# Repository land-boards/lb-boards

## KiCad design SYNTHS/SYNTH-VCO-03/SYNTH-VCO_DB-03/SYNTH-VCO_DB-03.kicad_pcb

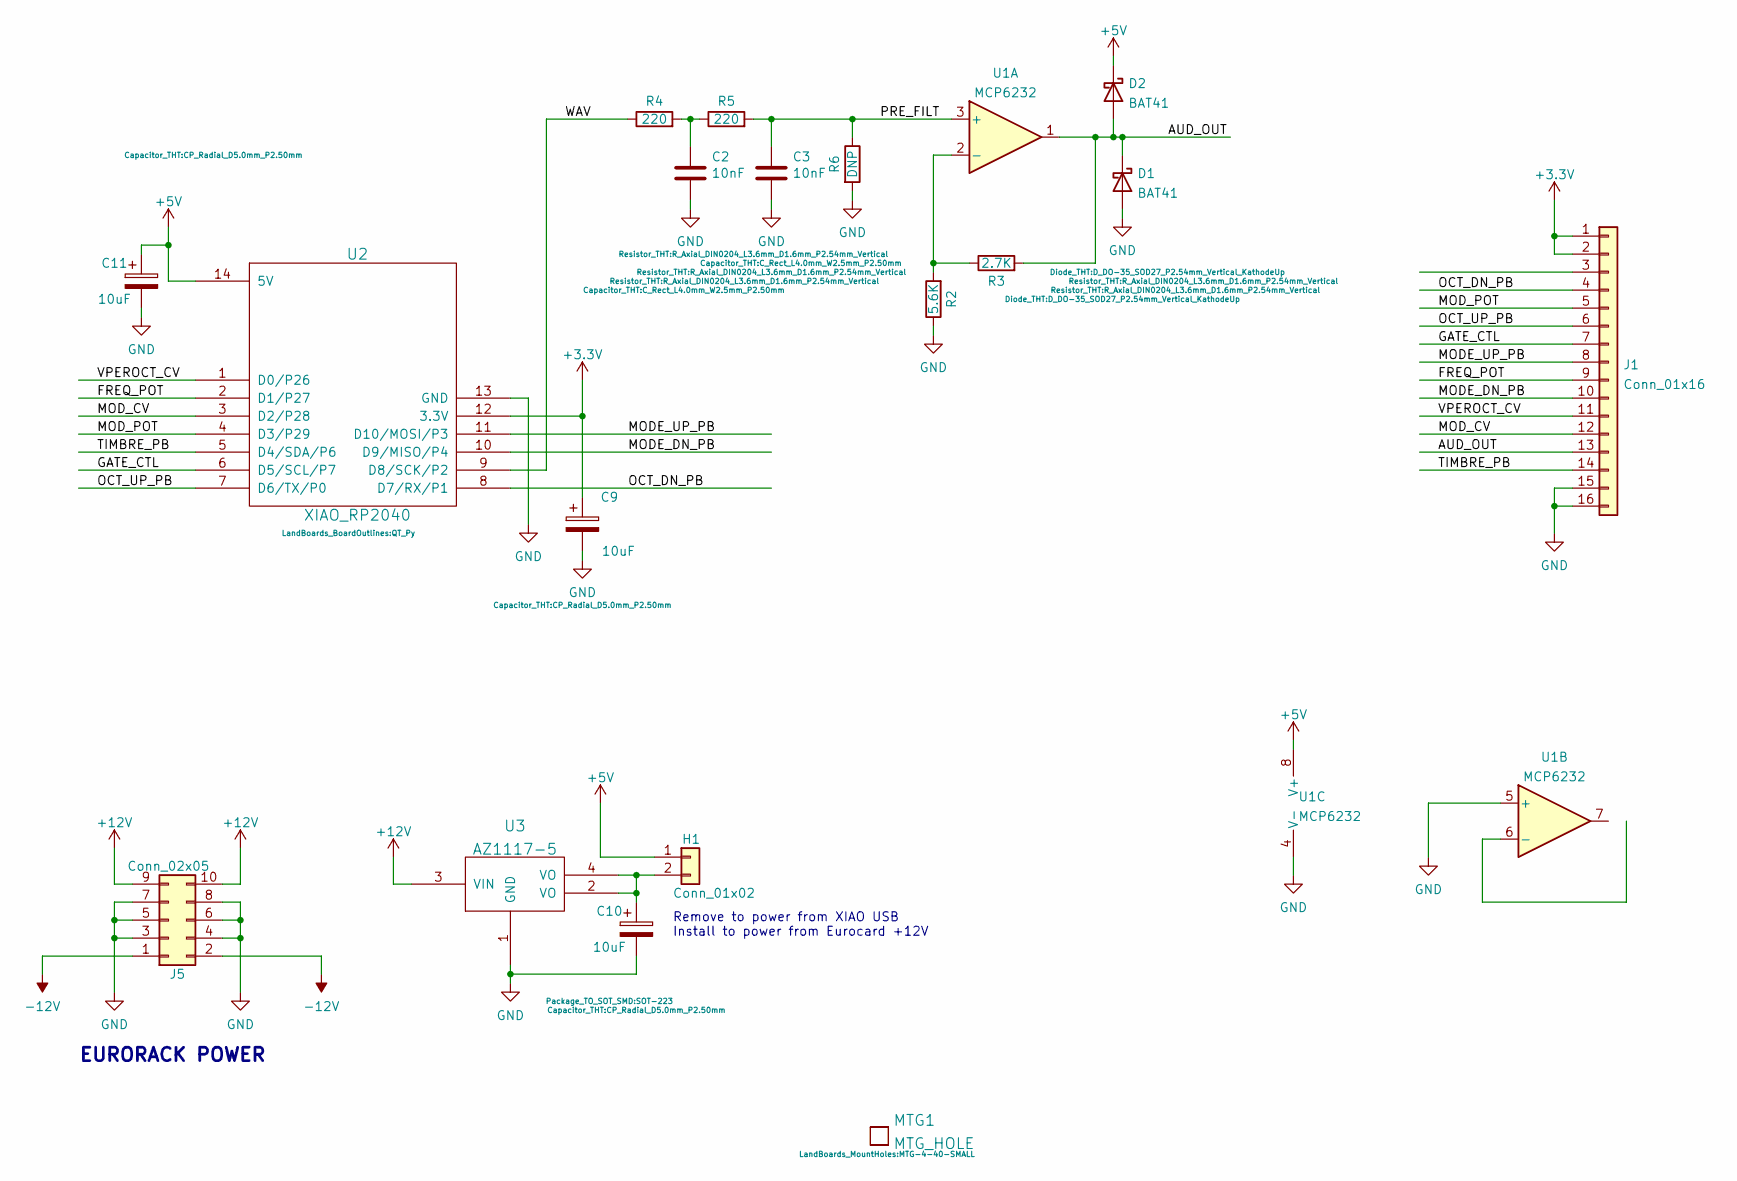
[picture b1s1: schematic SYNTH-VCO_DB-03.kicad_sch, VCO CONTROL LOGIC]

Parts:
C2, C3: 10nF; C_Rect_L4.0mm_W2.5mm_P2.50mm
C9, C10, C11: 10uF; CP_Radial_D5.0mm_P2.50mm
D1, D2: BAT41; D_DO-35_SOD27_P2.54mm_Vertical_KathodeUp
H1: Conn_01x02; PinHeader_1x02_P2.54mm_Vertical
J1: Conn_01x16; PinHeader_2x08_P2.54mm_Vertical
J5: Conn_02x05; IDC-Header_2x05_P2.54mm_Vertical
MTG1: MTG_HOLE; MTG-4-40-SMALL
R2: 5.6K; R_Axial_DIN0204_L3.6mm_D1.6mm_P2.54mm_Vertical
R3: 2.7K; R_Axial_DIN0204_L3.6mm_D1.6mm_P2.54mm_Vertical
R4, R5: 220; R_Axial_DIN0204_L3.6mm_D1.6mm_P2.54mm_Vertical
R6: DNP; R_Axial_DIN0204_L3.6mm_D1.6mm_P2.54mm_Vertical
U1: MCP6232; DIP-8_W7.62mm
U2: XIAO_RP2040; QT_Py
U3: AZ1117-5; SOT-223

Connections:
+3V3: C9.1, J1.1, J1.2, U2.12 (3.3V)
+5V: C11.1, D2.1 (K), H1.1, U1.8 (V+), U2.14 (5V)
+12V: J5.9, J5.10, U3.3 (VIN)
-12V: J5.1, J5.2
/AUD_OUT: D1.1 (K), D2.2 (A), J1.13, R3.2, U1.1
/FREQ_POT: J1.9, U2.2 (D1/P27)
/GATE_CTL: J1.7, U2.6 (D5/SCL/P7)
/MODE_DN_PB: J1.10, U2.10 (D9/MISO/P4)
/MODE_UP_PB: J1.8, U2.11 (D10/MOSI/P3)
/MOD_CV: J1.12, U2.3 (D2/P28)
/MOD_POT: J1.5, U2.4 (D3/P29)
/OCT_DN_PB: J1.4, U2.8 (D7/RX/P1)
/OCT_UP_PB: J1.6, U2.7 (D6/TX/P0)
/PRE_FILT: C3.1, R5.2, R6.1, U1.3 (+)
/TIMBRE_PB: J1.14, U2.5 (D4/SDA/P6)
/VPEROCT_CV: J1.11, U2.1 (D0/P26)
/WAV: R4.1, U2.9 (D8/SCK/P2)
GND: C2.2, C3.2, C9.2, C10.2, C11.2, D1.2 (A), J1.15, J1.16, J5.3, J5.4, J5.5, J5.6, J5.7, J5.8, R2.1, R6.2, U1.4 (V-), U1.5 (+), U2.13 (GND), U3.1 (GND)
unnamed: C2.1, R4.2, R5.1
unnamed: C10.1, H1.2, U3.2 (VO), U3.4 (VO)
unnamed: R2.2, R3.1, U1.2 (-)

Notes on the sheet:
EURORACK POWER
Remove to power from XIAO USB Install to power from Eurocard +12V

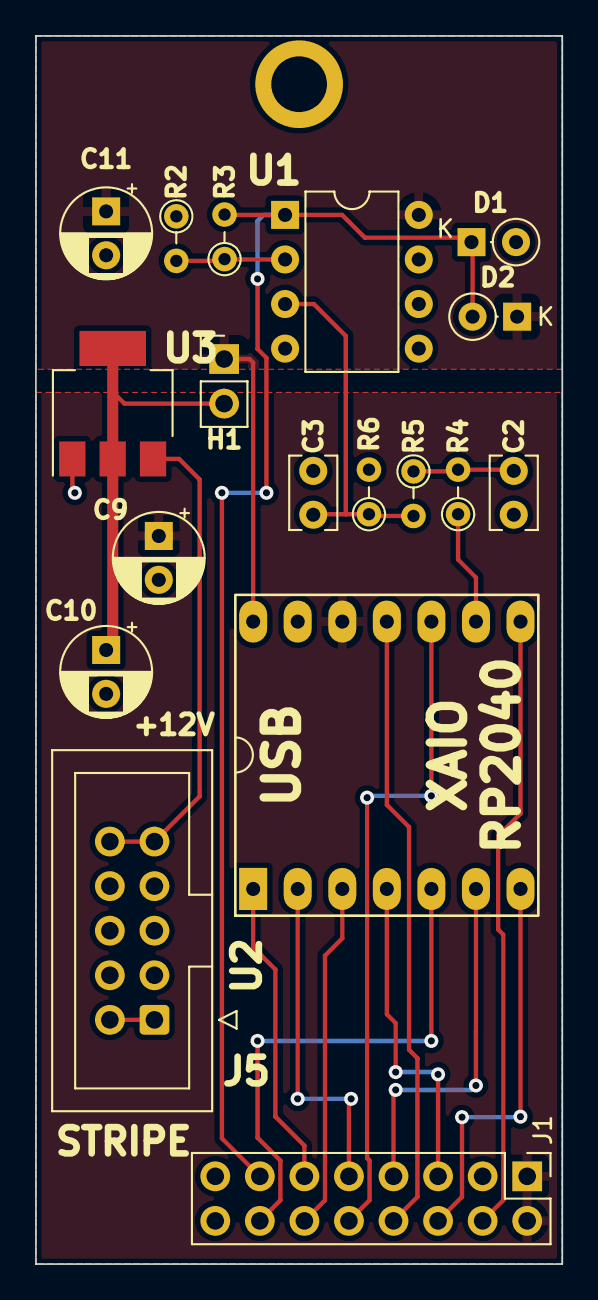
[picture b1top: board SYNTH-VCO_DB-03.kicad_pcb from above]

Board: 2 copper layers, 30.0 x 70.0 mm, 19 parts (0 on the bottom side), 21 nets.

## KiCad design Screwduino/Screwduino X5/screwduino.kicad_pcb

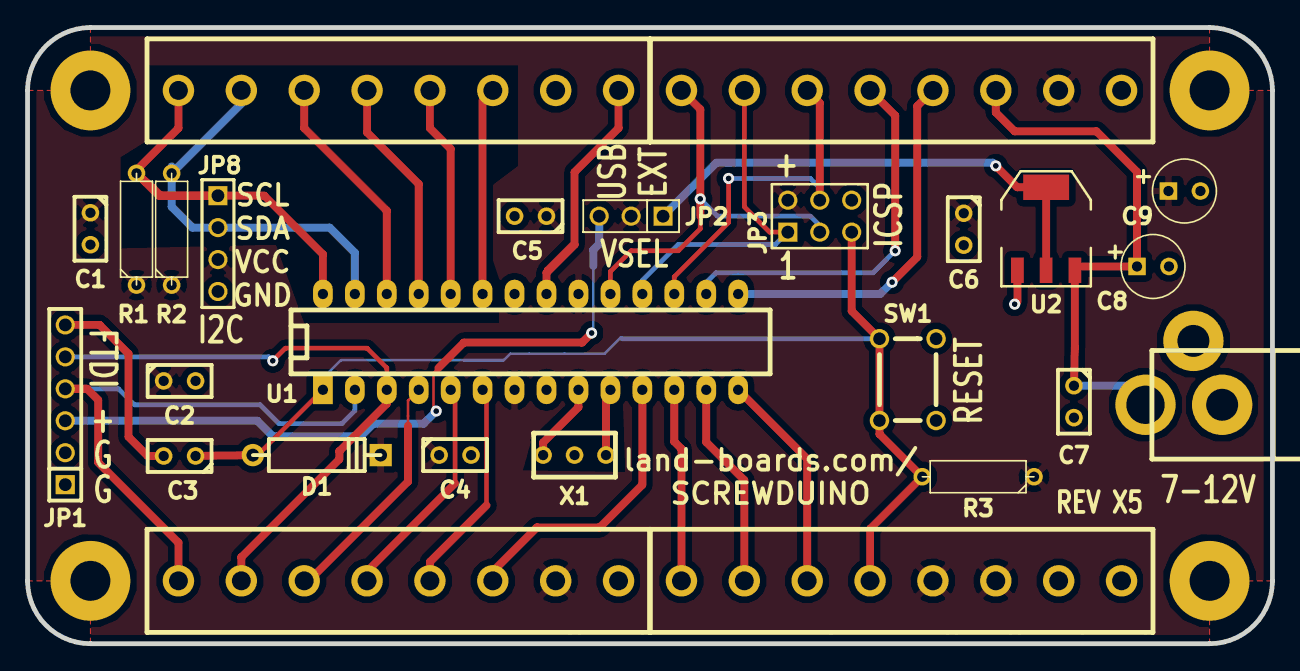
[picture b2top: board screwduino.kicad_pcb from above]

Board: 2 copper layers, 99.0 x 49.0 mm, 31 parts (0 on the bottom side), 30 nets.

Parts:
C1, C2, C3, C4, C5, C6, C7: 0.1uF; C1
C8, C9: 47uF; C1V5
D1: 1N4004; D4
JP1: CONN_6; PIN_ARRAY-6X1
JP2: CONN_3; PIN_ARRAY_3X1
JP3: CONN_3X2; pin_array_3x2
JP4, JP5, JP6, JP7: CONN_8; TB8-5MM
JP8: CONN_4; PIN_ARRAY_4x1
K1: JACK-3.5MM; JACK_2.1MM
MTG1, MTG2, MTG3, MTG4: CONN_1; MTG-4-40
R1, R2, R3: 10K; R3-5
SW1: SW_PUSH_OMRON; SW-PB-6MM
TESTED: VAL**; TEST_BLK-REAR
U1: ATMEGA328-P; DIP-28__300_ELL
U2: AP1117; SOT223
X1: 16MHz; RESON_3PIN

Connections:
+5V: C1.1, C2.1, C4.1, C5.1, C6.1, C9.1, D1.2, JP2.2, JP3.2, JP4.3, JP4.4, JP6.7, JP7.2, JP8.3, R1.1, R2.1, R3.1, U1.7, U1.20
/AD0: JP5.6, U1.23
/AD1: JP5.5, U1.24
/AD2: JP5.4, U1.25
/AD3: JP5.3, U1.26
/AREF: JP5.8, U1.21
/CX1: U1.10, X1.1
/CX2: U1.9, X1.3
/D0: JP1.4, JP7.8, U1.2
/D1: JP1.5, JP7.7, U1.3
/D2: JP7.6, U1.4
/D3: JP7.5, U1.5
/D4: JP7.4, U1.6
/D5: JP7.3, U1.11
/D6: JP4.8, U1.12
/D7: JP4.7, U1.13
/D8: JP4.6, U1.14
/D9: JP6.5, U1.15
/D10: JP6.4, U1.16
/D11: JP3.4, JP6.3, U1.17
/D12: JP3.1, JP6.2, U1.18
/D13: JP3.3, JP6.1, U1.19
/DTR*: C3.2, JP1.6
/RST*: C3.1, D1.1, JP3.5, JP4.5, R3.2, SW1.1, SW1.2, U1.1
/SCK: JP5.1, JP8.1, R1.2, U1.28
/SDA: JP5.2, JP8.2, R2.2, U1.27
/VIN: C7.1, C8.1, JP6.6, K1.1, U2.3
/VROUT: JP2.1, U2.2, U2.4
/VUSB: JP1.3, JP2.3
GND: C1.2, C2.2, C4.2, C5.2, C6.2, C7.2, C8.2, C9.2, JP1.1, JP1.2, JP3.6, JP4.1, JP4.2, JP5.7, JP6.8, JP7.1, JP8.4, K1.2, K1.3, SW1.3, SW1.4, U1.8, U1.22, U2.1, X1.2

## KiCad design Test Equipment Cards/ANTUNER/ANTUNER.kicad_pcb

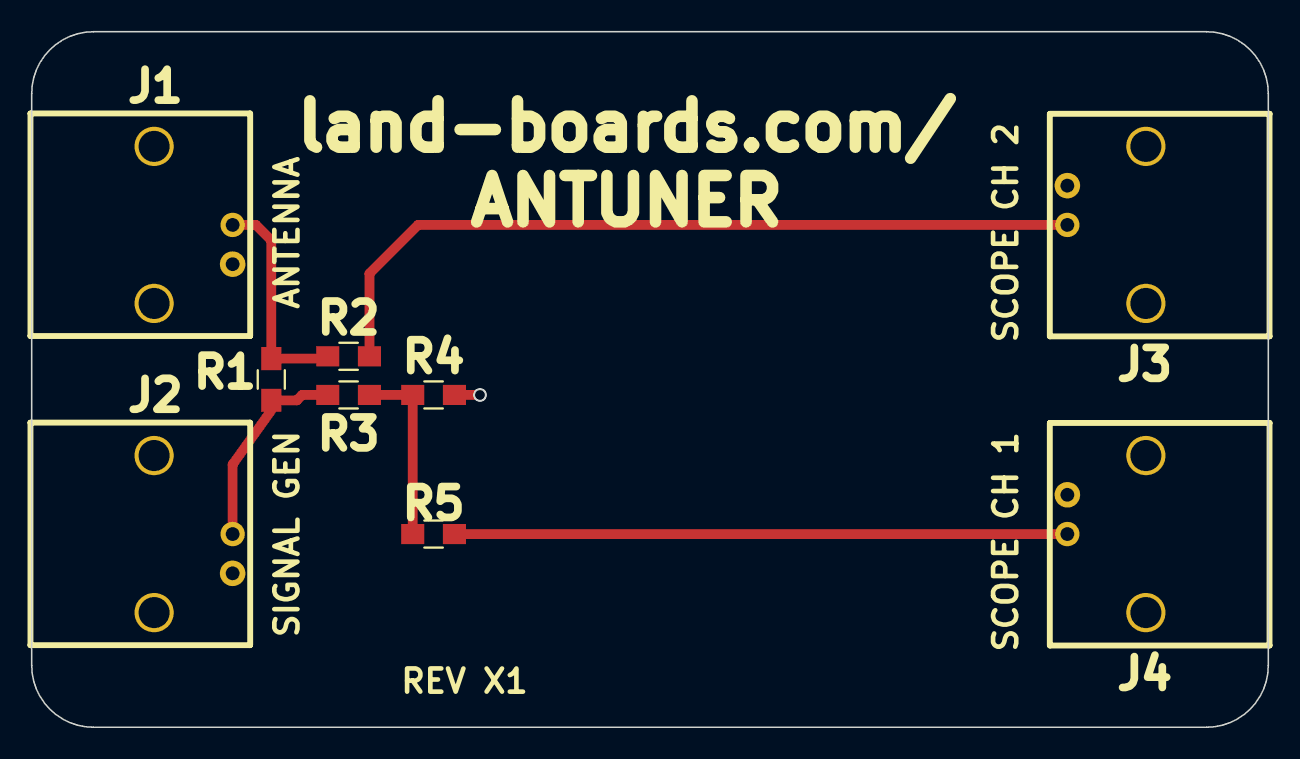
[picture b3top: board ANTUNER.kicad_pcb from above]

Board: 2 copper layers, 80.0 x 45.0 mm, 10 parts (0 on the bottom side), 6 nets.

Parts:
J1, J2, J3, J4: BNC; BNC-RT
R1, R3, R4: 50; R_0805_HandSoldering
R2, R5: 1K; R_0805_HandSoldering
TESTED: COUPON; TEST_BLK-REAR

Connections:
GND: J1.2, J2.2, J3.2, J4.2, R4.2
unnamed: J1.1, R1.2, R2.1
unnamed: J2.1, R1.1, R3.1
unnamed: J3.1, R2.2
unnamed: J4.1, R5.1
unnamed: R3.2, R4.1, R5.2

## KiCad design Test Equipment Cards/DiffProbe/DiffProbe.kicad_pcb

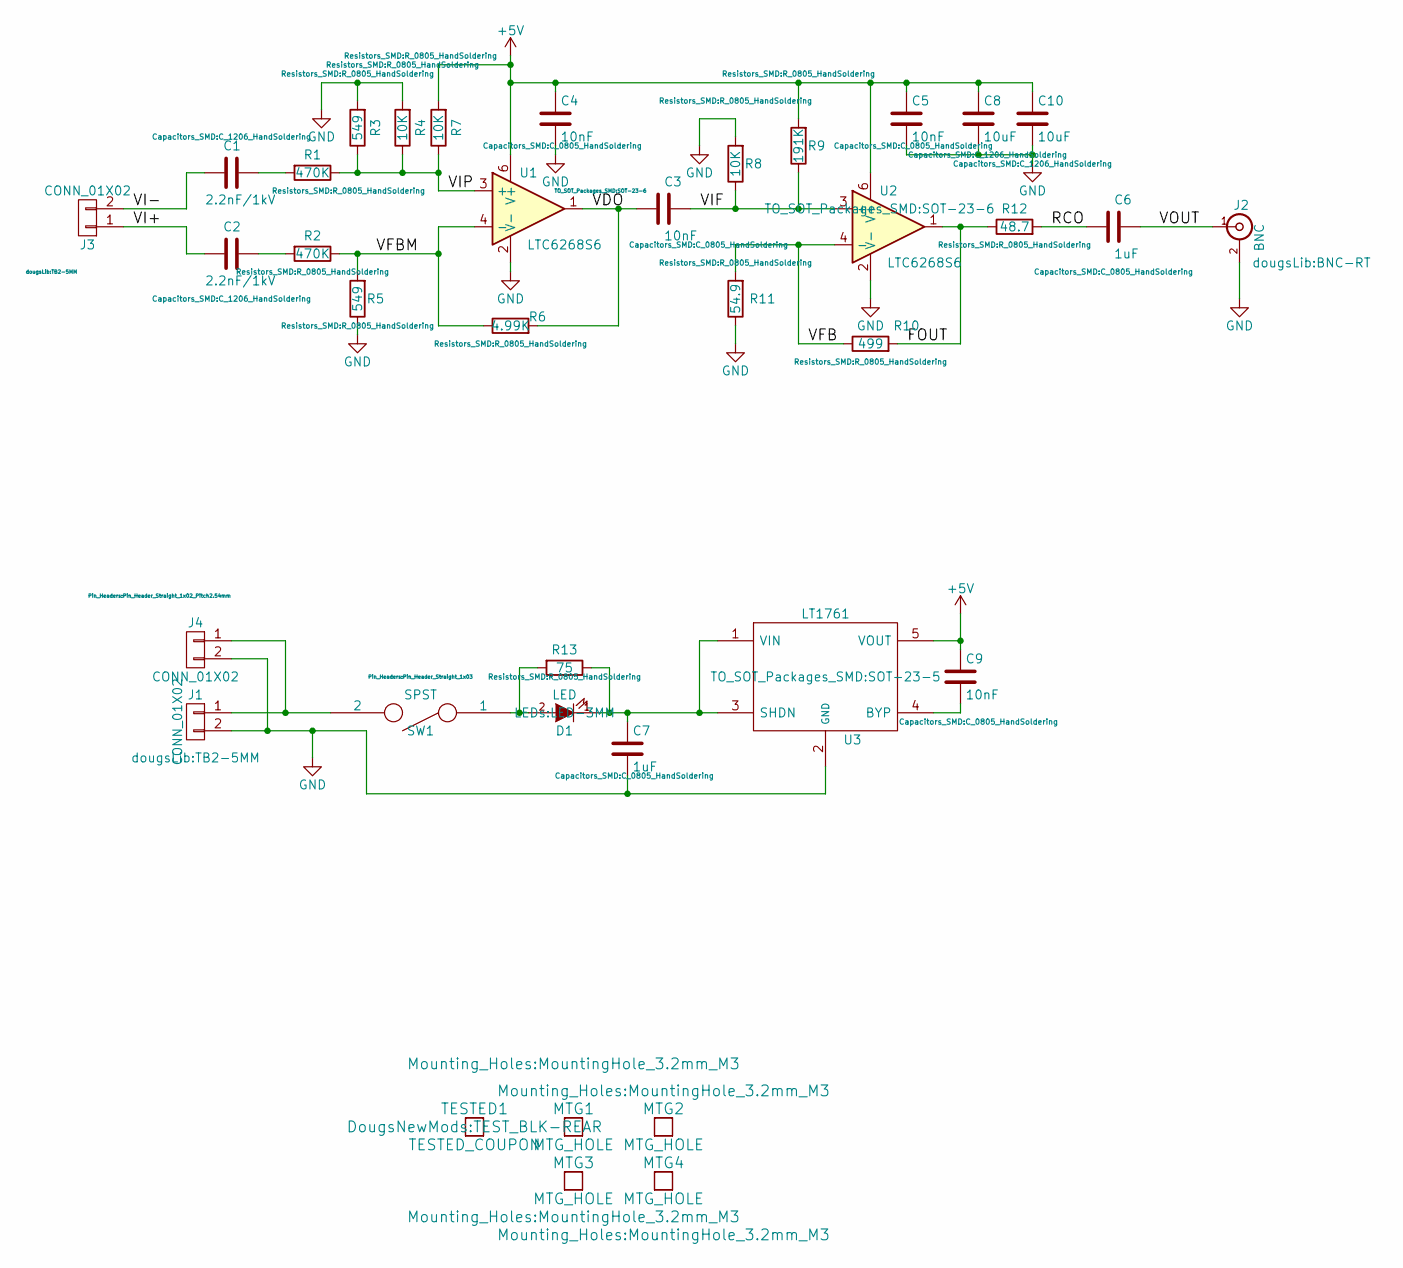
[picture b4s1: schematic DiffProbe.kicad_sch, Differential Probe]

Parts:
C1, C2: 2.2nF/1kV; C_1206_HandSoldering
C3, C4, C5, C9: 10nF; C_0805_HandSoldering
C6, C7: 1uF; C_0805_HandSoldering
C8, C10: 10uF; C_1206_HandSoldering
D1: LED; LED-3MM
J1, J3: CONN_01X02; TB2-5MM
J2: BNC; BNC-RT
J4: CONN_01X02; Pin_Header_Straight_1x02_Pitch2.54mm
MTG1, MTG2, MTG3, MTG4: MTG_HOLE; MountingHole_3.2mm_M3
R1, R2: 470K; R_0805_HandSoldering
R3, R5: 549; R_0805_HandSoldering
R4, R7, R8: 10K; R_0805_HandSoldering
R6: 4.99K; R_0805_HandSoldering
R9: 191K; R_0805_HandSoldering
R10: 499; R_0805_HandSoldering
R11: 54.9; R_0805_HandSoldering
R12: 48.7; R_0805_HandSoldering
R13: 75; R_0805_HandSoldering
SW1: SPST; Pin_Header_Straight_1x03
TESTED1: TESTED_COUPON; TEST_BLK-REAR
U1, U2: LTC6268S6; SOT-23-6
U3: LT1761; SOT-23-5

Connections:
+5V: C4.1, C5.1, C8.1, C9.1, C10.1, R7.2, R9.2, U1.6 (V+), U2.6 (V+), U3.5 (VOUT)
/FOUT: R10.2, R12.1, U2.1
/RCO: C6.2, R12.2
/VDO: C3.2, R6.2, U1.1
/VFB: R10.1, R11.2, U2.4 (-)
/VFBM: R2.1, R5.2, R6.1, U1.4 (-)
/VI+: C2.2, J3.1
/VI-: C1.2, J3.2
/VIF: C3.1, R8.1, R9.1, U2.3 (+)
/VIP: R1.1, R3.1, R4.1, R7.1, U1.3 (+)
/VOUT: C6.1, J2.1 (In)
GND: C4.2, C5.2, C7.2, C8.2, C10.2, J1.2, J2.2 (Ext), J4.2, R3.2, R4.2, R5.1, R8.2, R11.1, U1.2 (V-), U2.2 (V-), U3.2 (GND)
unnamed: C1.1, R1.2
unnamed: C2.1, R2.2
unnamed: C7.1, D1.1 (K), R13.1, U3.1 (VIN), U3.3 (SHDN)
unnamed: C9.2, U3.4 (BYP)
unnamed: D1.2 (A), R13.2, SW1.1
unnamed: J1.1, J4.1, SW1.2

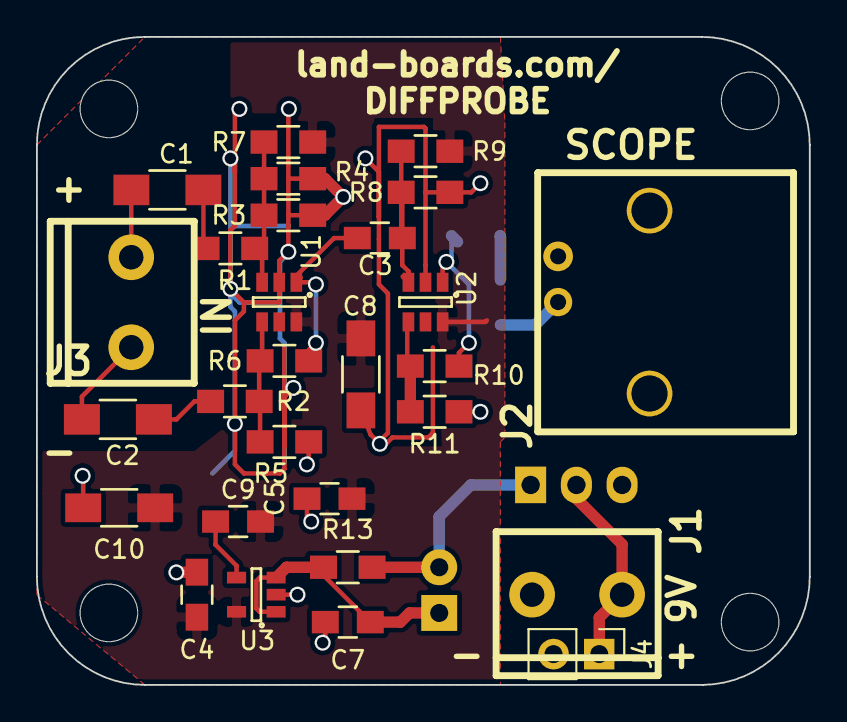
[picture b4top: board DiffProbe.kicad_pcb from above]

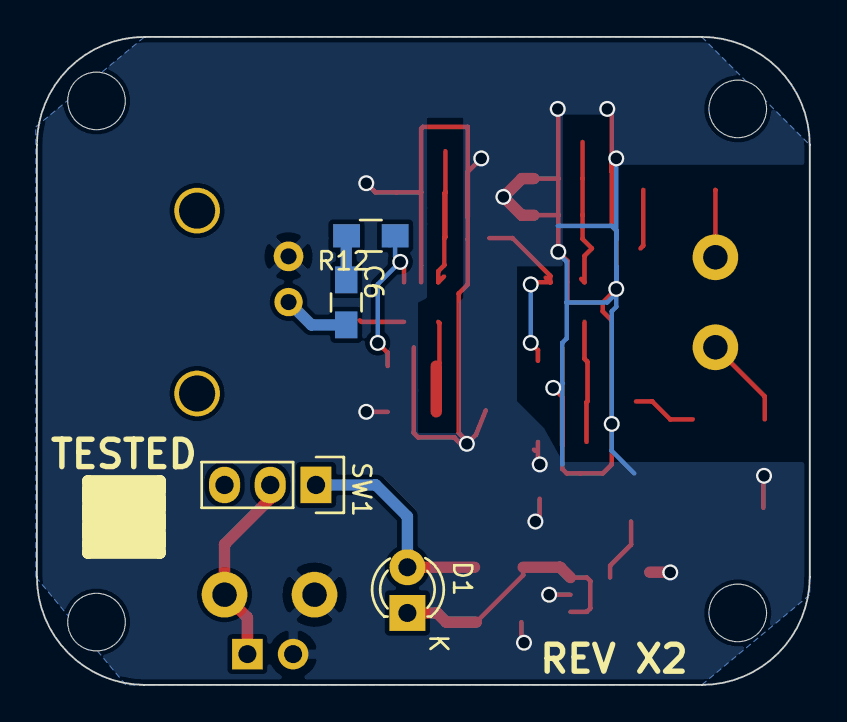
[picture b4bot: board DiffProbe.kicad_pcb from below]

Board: 2 copper layers, 42.9 x 36.0 mm, 37 parts (4 on the bottom side), 18 nets.

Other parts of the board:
TESTED: TESTED_COUPON; TEST_BLK-REAR
